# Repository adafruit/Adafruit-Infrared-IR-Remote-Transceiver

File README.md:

## Adafruit Infrared IR Remote Transceiver - STEMMA JST PH 2mm - 940nm Emitter + 38KHz Receiver PCB

<a href="http://www.adafruit.com/products/5990"><br/>
Click here to purchase one from the Adafruit shop</a>

PCB files for the Adafruit Infrared IR Remote Transceiver - STEMMA JST PH 2mm - 940nm Emitter + 38KHz Receiver. 

Format is EagleCAD schematic and board layout
* https://www.adafruit.com/product/5990

### Description

We've got a high-powered infrared emitter board, and a super-sensitive infrared remote receiver board - but why buy two boards when you can pick up one that does both? This board is the Adafruit Infrared Tranceiver breakout, which can transmit and receiver 940nm remote control data in one handy solder-free package.

Please Note: to make this board easy to use, we have both solder-able breakout pads and also a JST PH 4-pin cable. We often use JST PH cables for I2C but this board does not use I2C - the white wire is data from a microcontroller to be emitted over the IR LED, the green wire is demodulated IR remote signal data to a microcontroller. The black wire is ground, red wire is 3V~5V power and logic level.

For the emitter half, we use the same schematic and setup as our "High Power IR LED Emitter" breakout, with an onboard N-Channel FET driver, to blast 100mA-200mA of current pulsing through each LED for 10+ meters of range! One LED is vertical and one is horizontal so you get tons of coverage. If powering with 5V, the board will draw about 200mA per LED (400mA total) when pulsing on. If powering with 3V the board will draw about 100mA per LED (200mA total). Since you can't see IR with a human eyeball, we have a small yellow LED labeled 'IN' that will blink when the IR LEDs are on.

For the receiver half, we use the same 'vertical' IR sensor in our "IR Receiver breakout"  The sensor is designed to recognize remote control style modulated signal at 38KHz and 940nm wavelength. The demodulated IR envelope is piped out the OUT labeled pin into your microcontroller which will then need to decode it. To make debugging easy, there's a second yellow LED labelled "OUT" that will blink when data is received.

Each STEMMA board is a fully assembled and tested PCB, but no cable. No soldering is required to use it, but you will need to pick up a 2mm pitch, 4-pin STEMMA JST PH cable. Alternatively, if you do want to solder, there's a 0.1" spaced header for power/ground/signals.

Note that this board is specifically for receiving 940nm 38KHz IR remote control signals - it isn't going to work for proximity/distance sensing or other frequency signals. The signal must be read by a microcontroller that has pulse-input reading capabilities - basically just check that it supports common IR Receiver connectivity and decoding. Sometimes you need to use special code or pins.

### License

Adafruit invests time and resources providing this open source design, please support Adafruit and open-source hardware by purchasing products from [Adafruit](https://www.adafruit.com)!

Designed by Limor Fried/Ladyada for Adafruit Industries.

Creative Commons Attribution/Share-Alike, all text above must be included in any redistribution. 
See license.txt for additional details.

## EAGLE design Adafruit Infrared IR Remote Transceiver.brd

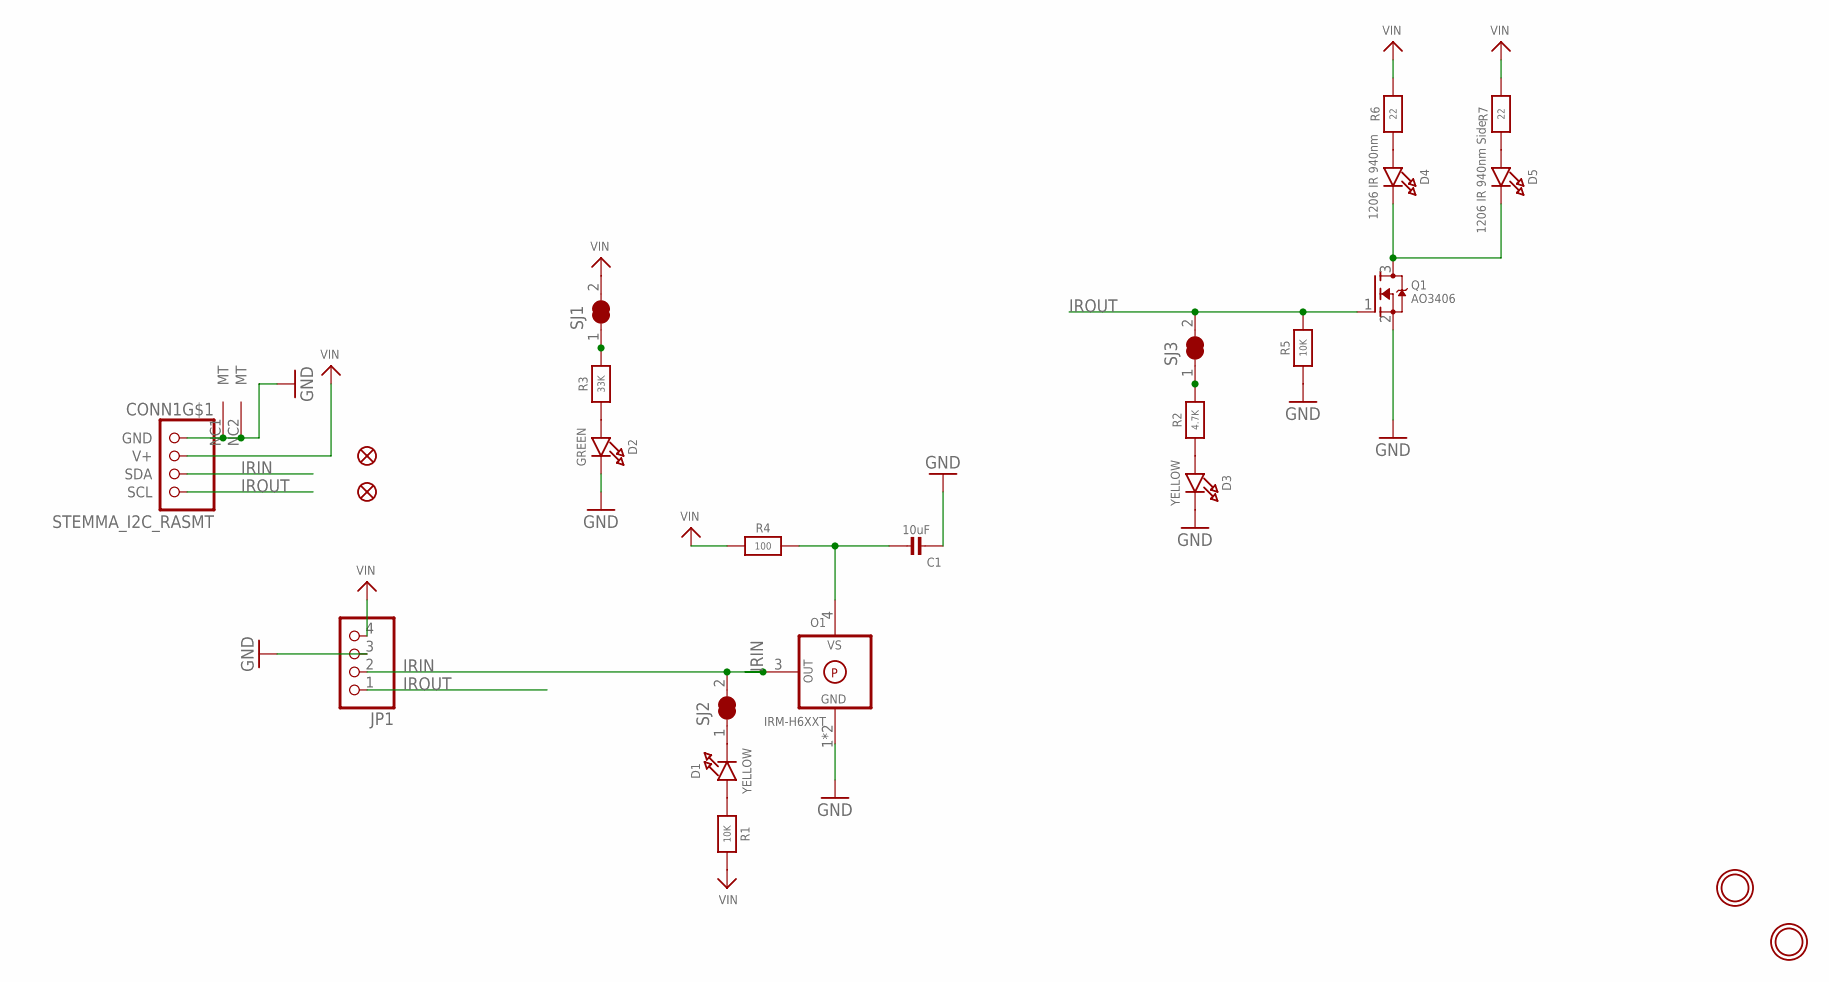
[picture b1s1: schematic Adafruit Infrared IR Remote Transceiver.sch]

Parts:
C1: 10uF; 0805-NO
CONN1: STEMMA_I2C_RASMT; JSTPH4
D1, D3: YELLOW; CHIPLED_0603_NOOUTLINE
D2: GREEN; CHIPLED_0603_NOOUTLINE
D4: 1206 IR 940nm; CHIPLED_1206
D5: 1206 IR 940nm Side; LED_1206_SIDE
FID2, FID3: FIDUCIAL_1MM
JP1: HEADER-1X476MIL; 1X04_ROUND_76
O1: IRM-H6XXT
Q1: AO3406; SOT23-WIDE
R1, R5: 10K; 0603-NO
R2: 4.7K; 0603-NO
R3: 33K; 0603-NO
R4: 100; 0603-NO
R6, R7: 22; 0603-NO
SJ1, SJ2, SJ3: SOLDERJUMPER_CLOSED; SOLDERJUMPER_CLOSEDWIRE
U$1, U$8: MOUNTINGHOLE2.5; MOUNTINGHOLE_2.5_PLATED

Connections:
GND: C1.2, CONN1.1 (GND), CONN1.NC1 (MT), CONN1.NC2 (MT), D2.C, D3.C, JP1.3, O1.1 (GND), O1.2 (GND), Q1.2 (S), R5.1
IRIN: CONN1.3 (SDA), JP1.2, O1.3 (OUT), SJ2.2
IROUT: CONN1.4 (SCL), JP1.1, Q1.1 (G), R5.2, SJ3.2
unnamed: R3.2, SJ1.1
unnamed: D1.A, R1.1
unnamed: D1.C, SJ2.1
unnamed: C1.1, O1.4 (VS), R4.2
unnamed: R2.2, SJ3.1
unnamed: D3.A, R2.1
unnamed: D4.C, D5.C, Q1.3 (D)
unnamed: D4.A, R6.1
unnamed: D5.A, R7.1
unnamed: D2.A, R3.1
VIN: CONN1.2 (V+), JP1.4, R1.2, R4.1, R6.2, R7.2, SJ1.2

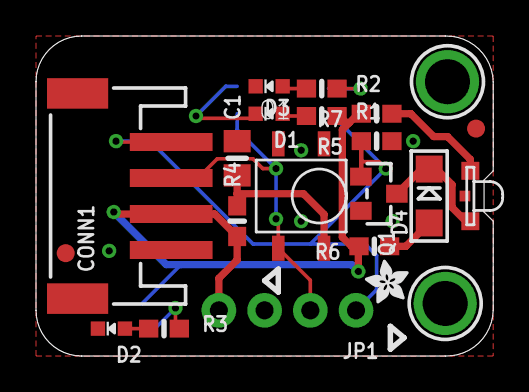
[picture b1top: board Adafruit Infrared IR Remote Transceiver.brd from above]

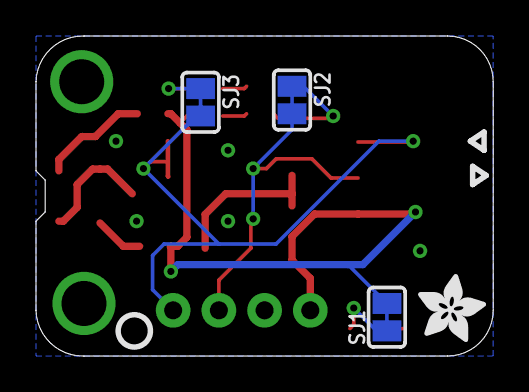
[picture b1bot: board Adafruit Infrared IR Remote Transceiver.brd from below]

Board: 2 copper layers, 25.4 x 17.8 mm, 45 parts (15 on the bottom side), 14 nets.

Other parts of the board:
PLABEL0: PLABEL0
PLABEL1: PLABEL1
PLABEL2: PLABEL2
PLABEL3: PLABEL3
PLABEL4: PLABEL4
PLABEL5: PLABEL5
PLABEL6: PLABEL6
PLABEL7: PLABEL7
PLABEL8: PLABEL8
PLABEL9: PLABEL9
PLABEL10: PLABEL10
PLABEL11: PLABEL11
PLABEL12: PLABEL12
PLABEL13: PLABEL13
PLABEL14: PLABEL14
PLABEL15: PLABEL15
PLABEL16: PLABEL16
PLABEL17: PLABEL17
U$5: PCBFEAT-REV-040
U$12: ADAFRUIT_3.5MM
U$13: ADAFRUIT_2.5MM

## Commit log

2024-07-08 cookiecutter

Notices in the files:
parts and their libraries:
microbuilder: This work is placed in the public domain, and may be freely used for commercial and non-commercial work with the following conditions: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
